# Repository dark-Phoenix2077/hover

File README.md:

# Hover
A fully custom mini racing/stunt drone with ML-assisted balancing, automatic stunts, and some level of autonomous operation without costly cameras or GPS.

## Why I built this

I wanted a challenge that forced me to learn PCB design and embedded firmware from 
scratch, but also let me apply the area I already know well - machine learning. Designing
a drone from a blank schematic, writing every driver by hand, and then training a custom 
tiny ML model felt like the right way to do all of that at once. My goal was simply to push my first ever hardware project as far as I could, not to have a completely polished project.

## What the project is

Hover is a tiny brushed micro quadcopter built entirely from custom hardware and
firmware. There is no off-the-shelf flight controller, no commercial RC receiver, and no
pre-written driver code. Everything was written/designed from scratch by me.

The system has two PCBs:

Flight Controller (FC): A 4-layer X-shaped PCB with a motor in each corner. It runs an
STM32F103C8T6 at 72MHz, an ICM-42688-P IMU over SPI, a BK2423 2.4GHz RF transceiver, 
and four brushed motor drive circuits.

Remote Control (RC): A 2-layer PCB inside a 3D-printed enclosure. It uses
the same STM32F103C8T6 and BK2423 RF ICs. It has two analog joysticks (ADC + DMA) for
throttle, yaw, pitch, and roll, and eight buttons which are used for arming, auto take-off, auto land,
return-to-home, a 360-degree flip trigger (one of my goals for this was to have some kind of smart one-button trick, and for this goal I settled on the 360 flip), and three spares for future use.

apart from that, this repository also includes:

ML Pipeline: A training and conversion pipeline for an onboard stabilisation model.
Training data will be collected from real flight telemetry once the hardware is
bought. The model will be converted to TFLite and dropped directly into the
FC firmware, which already has the inference code in place and waiting.

CAD: Both the drone body and RC enclosure were designed in Onshape. The drone frame
is a minimal 2-shell design with motor mounts, battery tray, and canopy, with both shells 
sandwiching the PCB in the middle. The RC enclosure uses the same 2-shell design with joystick 
cutouts, button extenders, and a battery bay below the PCB.

Firmware: Firmware created for both the FC and RC in STM32 CubeMX and CubeIDE, all firmware should work but is untested as I do not have the hardware right now. additionally, the ML inference file is writtenbut will not work until I create the .tflite model file.

BOM: A BOM generated from kicad for the FC & the RC and also other parts (excluding 3D printed parts and assorted screws). I will likely be purchasing all of these myself, and this is not completely final.

## Build Photos:

# Bill of Materials
FC

* Note that MPU-6050 is significantly cheaper locally, and that is why I chose to use it despite cheaper alternatives

| Reference | Component | Qty | Package | LCSC | Price/Unit |
|---|---|---|---|---|---|
| U2 | STM32F103C8T6 | 1 | LQFP-48 | https://www.lcsc.com/product-detail/C8734.html | $1.65 |
| U3 | MPU-6050 | 1 | QFN-24 | https://www.lcsc.com/product-detail/C24112.html | $6.88 |
| U4 | BK2423 | 1 | QFN-20 | https://www.lcsc.com/search?q=BK2423 | ~$0.80 |
| U1 | AMS1117-3.3 | 1 | SOT-223 | https://www.lcsc.com/product-detail/C347222.html | ~$0.10 |
| Y1, Y2 | 16MHz Crystal | 2 | SMD 3225-4Pin | https://www.lcsc.com/product-detail/C13738.html | $0.30 |
| Q1–Q4 | SI2300 MOSFET | 4 | SOT-23 | https://www.lcsc.com/product-detail/C6285728.html | $0.01 |
| D1–D4 | 1N4148 Flyback Diode | 4 | SOD-323 | https://www.lcsc.com/product-detail/C2972761.html | $0.006 |
| J1 | Battery Connector (1S) | 1 | JST-PH 2pin | https://www.lcsc.com/product-detail/C295747.html | ~$0.08 |
| J2–J5 | Motor Connector | 4 | JST-PH 2pin | https://www.lcsc.com/product-detail/C295747.html | ~$0.08 |
| J6 | SWD Header | 1 | 2.54mm 1×4 | https://www.lcsc.com/product-detail/C124375.html | ~$0.05 |
| J7 | Charge Port | 1 | Barrel Jack SMD | www.lcsc.com/product-detail/C16214.html | ~$0.20 |
| SW1 | Slide Switch | 1 | SMD SPDT | https://www.lcsc.com/product-detail/C431541.html | ~$0.12 |
| TP1–TP5 | Test Point 1.5mm | 5 | Pad D1.5mm | https://www.lcsc.com/search?q=testpoint+1.5mm | ~$0.02 |
| C1, C3, C19, C21 | 10µF Cap | 4 | 0805 | https://www.lcsc.com/search?q=0805+capacitor | ~$0.002 |
| C2, C4–C10, C14–C18, C20, C24 | 100nF Cap | 15 | 0402 | https://www.lcsc.com/search?q=0402+capacitor | ~$0.002 |
| C11 | 1µF Cap | 1 | 0402 | https://www.lcsc.com/search?q=0402+capacitor | ~$0.002 |
| C12, C13, C22, C23 | 22pF Cap | 4 | 0402 | https://www.lcsc.com/search?q=0402+capacitor | ~$0.002 |
| R1, R6, R8, R10, R12 | 10kΩ Resistor | 5 | 0402 | https://www.lcsc.com/search?q=0402+resistor | ~$0.002 |
| R2, R3 | 4.7kΩ Resistor | 2 | 0402 | https://www.lcsc.com/search?q=0402+resistor | ~$0.002 |
| R4 | 22kΩ Resistor | 1 | 0402 | https://www.lcsc.com/search?q=0402+resistor | ~$0.002 |
| R5, R7, R9, R11 | 100Ω Resistor | 4 | 0402 | https://www.lcsc.com/search?q=0402+resistor | ~$0.002 |

RC

| Reference | Component | Qty | Package | LCSC | Price/Unit |
|---|---|---|---|---|---|
| U4 | STM32F103C8T6 | 1 | LQFP-48 | https://www.lcsc.com/product-detail/C8734.html | $1.65 |
| U5 | BK2423 | 1 | QFN-20 | https://www.lcsc.com/search?q=BK2423 | ~$0.80 |
| U1 | AMS1117-3.3 | 1 | SOT-223 | https://www.lcsc.com/product-detail/C347222.html | ~$0.10 |
| Y2, Y3 | 16MHz Crystal | 2 | SMD 3225-4Pin | https://www.lcsc.com/product-detail/C13738.html | $0.30 |
| BZ1 | Buzzer | 1 | 12×9.5mm THT | — | — |
| D1 | LED Indicator | 1 | THT D1.8mm | — | — |
| J1 | Battery Connector (1S) | 1 | JST-PH 2pin | https://www.lcsc.com/product-detail/C295747.html | ~$0.08 |
| J2, J3 | Joystick Connector | 2 | 2.54mm 1×5 | — | — |
| J7 | SWD Header | 1 | 2.54mm 1×4 | https://www.lcsc.com/product-detail/C124375.html | ~$0.05 |
| J8 | Charge Port | 1 | Barrel Jack THT | https://www.lcsc.com/product-detail/C16214.html | ~$0.20 |
| SW1–SW8 | Push Button | 8 | THT 6mm | — | — |
| SW9 | Slide Switch | 1 | SMD SPDT | https://www.lcsc.com/product-detail/C431541.html | ~$0.12 |
| TP1 | Test Point 1.5mm (ANT) | 1 | Pad D1.5mm | https://www.lcsc.com/search?q=testpoint+1.5mm | ~$0.02 |
| C1, C3, C23, C31 | 10µF Cap | 4 | 0805 | https://www.lcsc.com/search?q=0805+capacitor | ~$0.002 |
| C2, C4, C14–C19, C24, C25, C28–C30 | 100nF Cap | 13 | 0402 | https://www.lcsc.com/search?q=0402+capacitor | ~$0.002 |
| C20 | 1µF Cap | 1 | 0402 | https://www.lcsc.com/search?q=0402+capacitor | ~$0.002 |
| C21, C22, C26, C27 | 22pF Cap | 4 | 0402 | https://www.lcsc.com/search?q=0402+capacitor | ~$0.002 |
| R1–R3 | 10kΩ Resistor | 3 | 0402 | https://www.lcsc.com/search?q=0402+resistor | ~$0.002 |
| R4 | 22kΩ Resistor | 1 | 0402 | https://www.lcsc.com/search?q=0402+resistor | ~$0.002 |
| R5, R6 | 100Ω Resistor | 2 | 0402 | https://www.lcsc.com/search?q=0402+resistor | ~$0.002 |

Other

* This list covers physical assembly components not part of either PCB
* It is not completely final - I made this off the top of my head, there are probably other components I forgot to identify
* It does not include miscellaneous screws or 3D printed parts

| Component | Qty | Notes | Price (est.) |
|---|---|---|---|
| Brushed coreless DC motors (8020) | 4 | 8×20mm form factor, 1S compatible | ~$2.00 each |
| 55mm micro quad propellers (CW) | 4 | Match motor shaft diameter | ~$0.50 each |
| 55mm micro quad propellers (CCW) | 4 | Match motor shaft diameter | ~$0.50 each |
| 1S LiPo battery — 150mAh (drone) | 1 | Fits battery tray in drone frame | ~$4.00 |
| 1S LiPo battery — 800mAh (RC) | 1 | Fits battery bay in RC enclosure | ~$6.00 |
| 31.25mm wire for 2.4GHz antenna (drone) | 1 | Bare solid-core wire, soldered to ANT test point on FC PCB; length = λ/4 at 2.4GHz | ~$0.10 |
| 31.25mm wire for 2.4GHz antenna (RC) | 1 | Same as above, for RC PCB ANT test point | ~$0.10 |
| Silicone motor wire (26AWG) | ~1m | Connects motors to PCB JST connectors | ~$1.00 |
| 1S LiPo charger (USB) | 1 | Compatible with JST-PH or barrel jack input | ~$5.00 |

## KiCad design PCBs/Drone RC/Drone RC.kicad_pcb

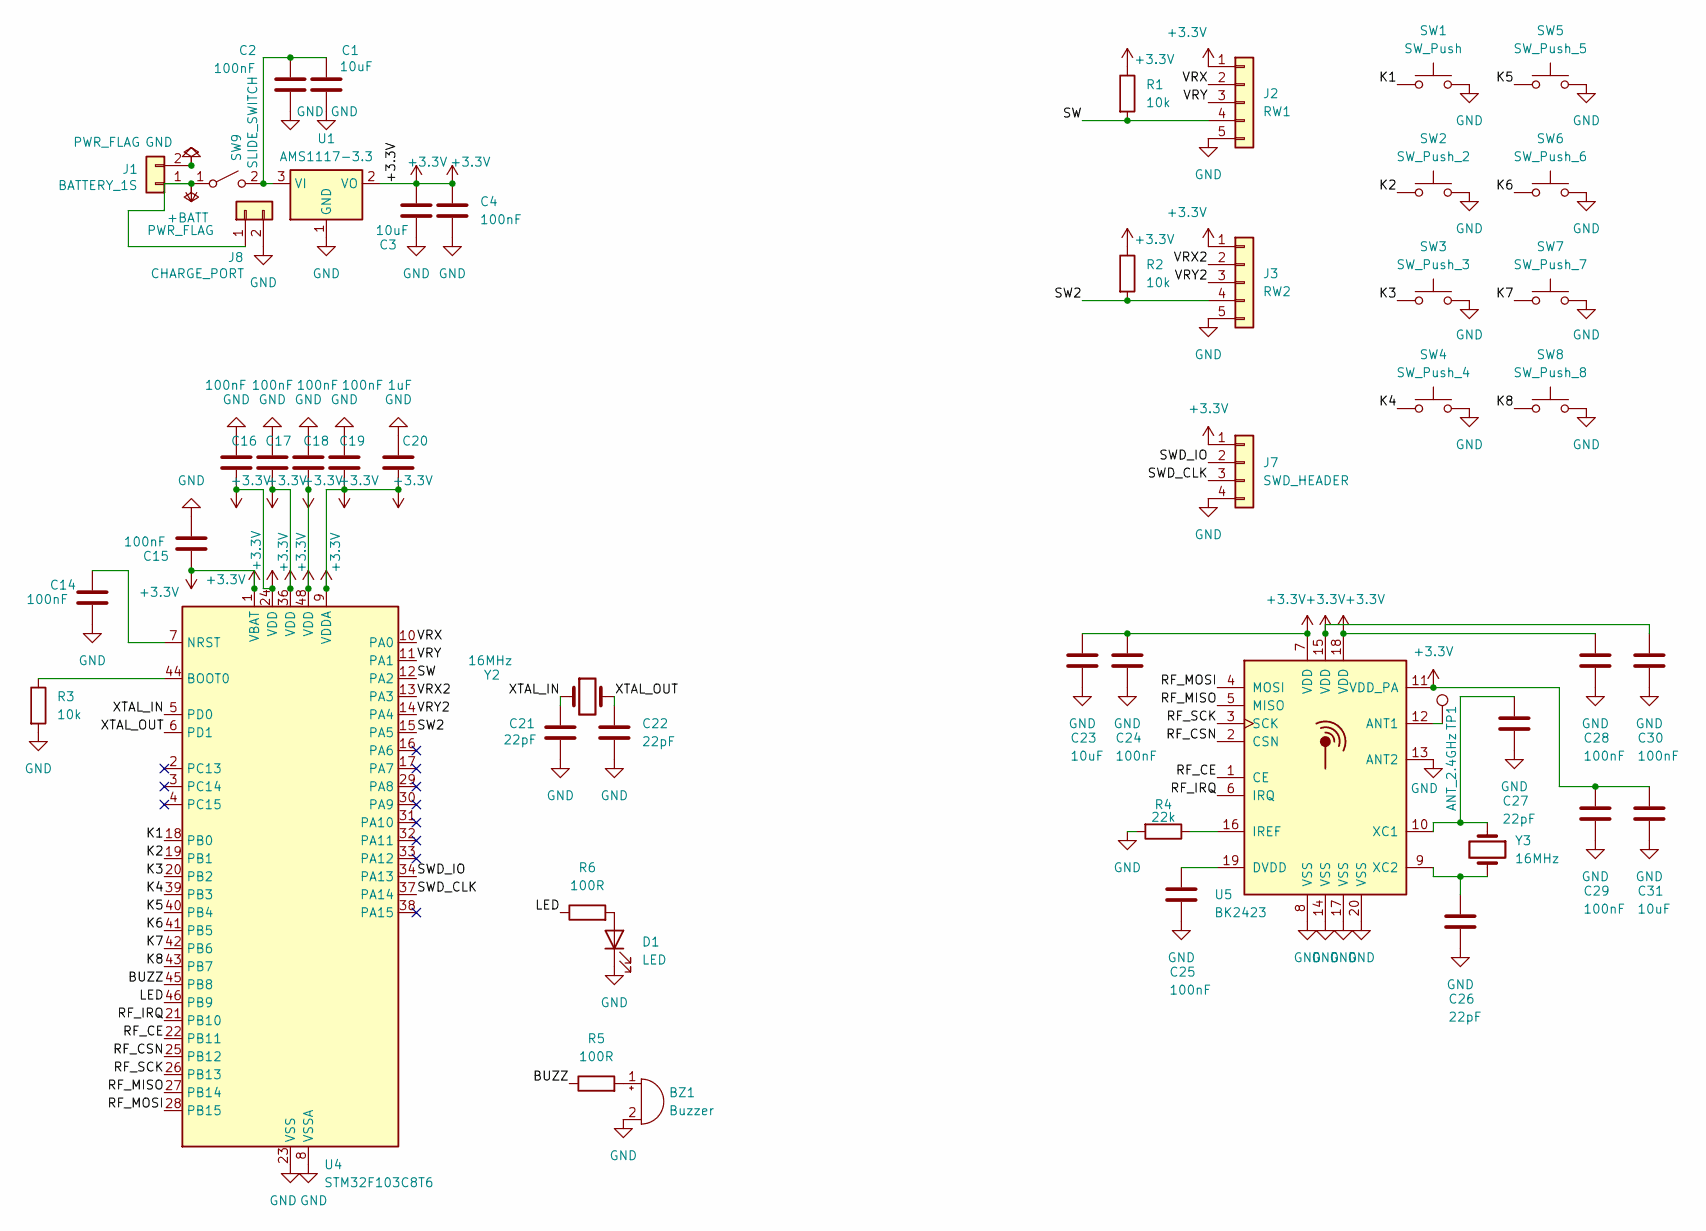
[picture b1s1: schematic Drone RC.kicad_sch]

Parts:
BZ1: Buzzer; Buzzer_12x9.5RM7.6
C1, C3, C23, C31: 10uF; C_0805_2012Metric
C2, C4, C14, C15, C16, C17, C18, C19, C24, C25, C28, C29, C30: 100nF; C_0402_1005Metric
C20: 1uF; C_0402_1005Metric
C21, C22, C26, C27: 22pF; C_0402_1005Metric
D1: LED; LED_D1.8mm_W1.8mm_H2.4mm_Horizontal_O1.27mm_Z1.6mm
J1: BATTERY_1S; JST_PH_B2B-PH-K_1x02_P2.00mm_Vertical
J2: RW1; PinHeader_1x05_P2.54mm_Vertical
J3: RW2; PinHeader_1x05_P2.54mm_Vertical
J7: SWD_HEADER; PinHeader_1x04_P2.54mm_Vertical
J8: CHARGE_PORT; BarrelJack_CUI_PJ-102AH_Horizontal
R1, R2, R3: 10k; R_0402_1005Metric
R4: 22k; R_0402_1005Metric
R5, R6: 100R; R_0402_1005Metric
SW1: SW_Push; SW_PUSH_6mm
SW2: SW_Push_2; SW_PUSH_6mm
SW3: SW_Push_3; SW_PUSH_6mm
SW4: SW_Push_4; SW_PUSH_6mm
SW5: SW_Push_5; SW_PUSH_6mm
SW6: SW_Push_6; SW_PUSH_6mm
SW7: SW_Push_7; SW_PUSH_6mm
SW8: SW_Push_8; SW_PUSH_6mm
SW9: SLIDE_SWITCH; SW_SPDT_CK_JS102011SAQN
TP1: ANT_2.4GHz; TestPoint_Pad_D1.5mm
U1: AMS1117-3.3; SOT-223-3_TabPin2
U4: STM32F103C8T6; LQFP-48_7x7mm_P0.5mm
U5: BK2423; QFN-20-1EP_4x4mm_P0.5mm_EP2.5x2.5mm
Y2, Y3: 16MHz; Crystal_SMD_3225-4Pin_3.2x2.5mm

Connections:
+3.3V: C3.1, C4.1, C15.1, C16.1, C17.1, C18.1, C19.1, C20.1, C23.1, C24.1, C28.1, C29.1, C30.1, C31.1, J2.1, J3.1, J7.1, R1.1, R2.1, U1.2 (VO), U4.1 (VBAT), U4.9 (VDDA), U4.24 (VDD), U4.36 (VDD), U4.48 (VDD), U5.7 (VDD), U5.11 (VDD_PA), U5.15 (VDD), U5.18 (VDD)
+BATT: J1.1, J8.1, SW9.1 (A)
/BUZZ: R5.1, U4.45 (PB8)
/K1: SW1.1, U4.18 (PB0)
/K2: SW2.1, U4.19 (PB1)
/K3: SW3.1, U4.20 (PB2)
/K4: SW4.1, U4.39 (PB3)
/K5: SW5.1, U4.40 (PB4)
/K6: SW6.1, U4.41 (PB5)
/K7: SW7.1, U4.42 (PB6)
/K8: SW8.1, U4.43 (PB7)
/LED: R6.1, U4.46 (PB9)
/RF_CE: U4.22 (PB11), U5.1 (CE)
/RF_CSN: U4.25 (PB12), U5.2 (CSN)
/RF_IRQ: U4.21 (PB10), U5.6 (IRQ)
/RF_MISO: U4.27 (PB14), U5.5 (MISO)
/RF_MOSI: U4.28 (PB15), U5.4 (MOSI)
/RF_SCK: U4.26 (PB13), U5.3 (SCK)
/SW: J2.4, R1.2, U4.12 (PA2)
/SW2: J3.4, R2.2, U4.15 (PA5)
/SWD_CLK: J7.3, U4.37 (PA14)
/SWD_IO: J7.2, U4.34 (PA13)
/VRX: J2.2, U4.10 (PA0)
/VRX2: J3.2, U4.13 (PA3)
/VRY: J2.3, U4.11 (PA1)
/VRY2: J3.3, U4.14 (PA4)
/XTAL_IN: C21.1, U4.5 (PD0), Y2.1
/XTAL_OUT: C22.1, U4.6 (PD1), Y2.2
GND: BZ1.2 (-), C1.2, C2.2, C3.2, C4.2, C14.2, C15.2, C16.2, C17.2, C18.2, C19.2, C20.2, C21.2, C22.2, C23.2, C24.2, C25.2, C26.2, C27.2, C28.2, C29.2, C30.2, C31.2, D1.1 (K), J1.2, J2.5, J3.5, J7.4, J8.2, R3.2, R4.2, SW1.2, SW2.2, SW3.2, SW4.2, SW5.2, SW6.2, SW7.2, SW8.2, U1.1 (GND), U4.8 (VSSA), U4.23 (VSS), U4.35 (VSS), U4.47 (VSS), U5.8 (VSS), U5.13 (ANT2), U5.14 (VSS), U5.17 (VSS), U5.20 (VSS)
unnamed: BZ1.1 (+), R5.2
unnamed: D1.2 (A), R6.2
unnamed: C1.1, C2.1, SW9.2 (B), U1.3 (VI)
unnamed: R3.1, U4.44 (BOOT0)
unnamed: C14.1, U4.7 (NRST)
unnamed: TP1.1 (1_1), U5.12 (ANT1)
unnamed: C25.1, U5.19 (DVDD)
unnamed: R4.1, U5.16 (IREF)
unnamed: C27.1, U5.10 (XC1), Y3.1
unnamed: C26.1, U5.9 (XC2), Y3.2

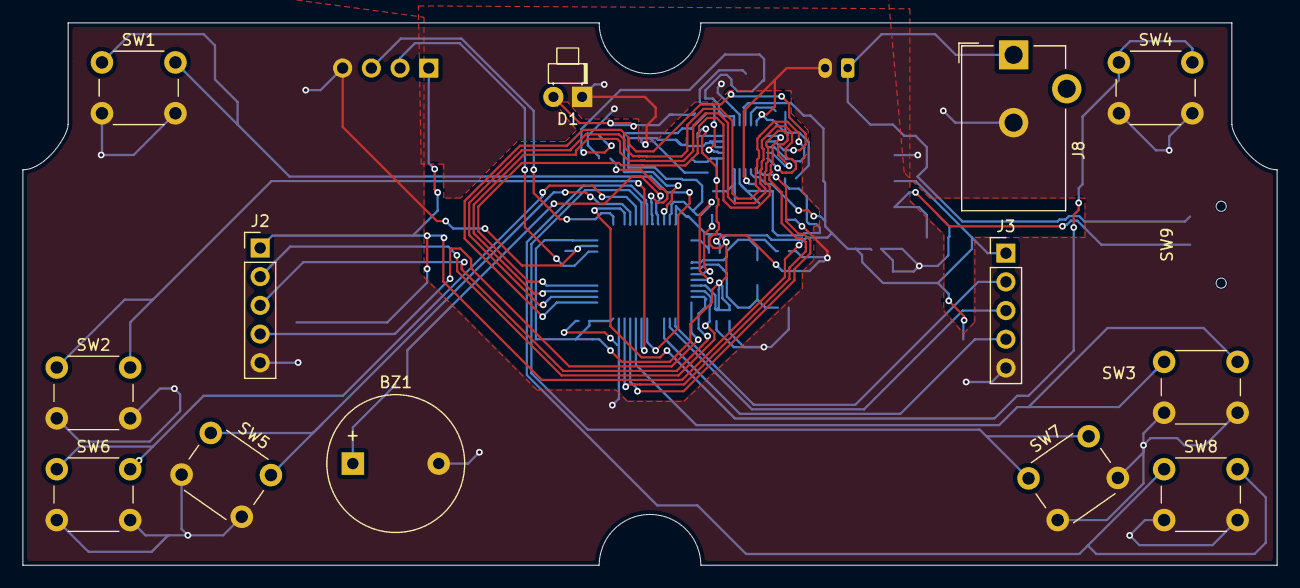
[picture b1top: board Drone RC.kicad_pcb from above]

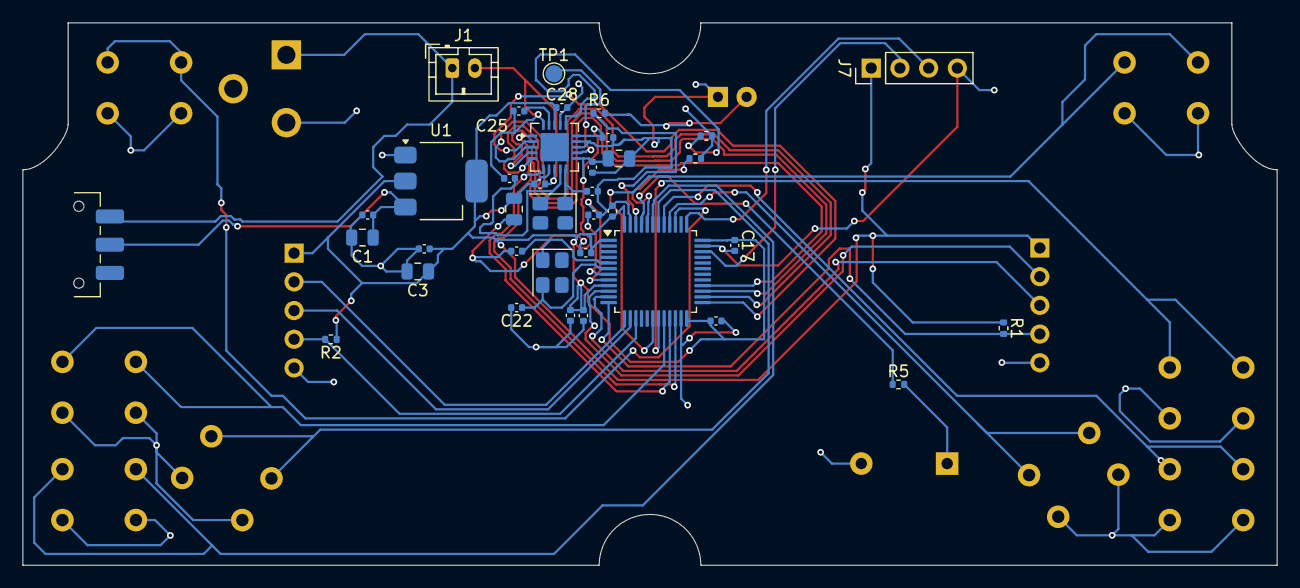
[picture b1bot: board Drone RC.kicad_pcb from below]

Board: 2 copper layers, 111.0 x 48.0 mm, 50 parts (37 on the bottom side), 39 nets.

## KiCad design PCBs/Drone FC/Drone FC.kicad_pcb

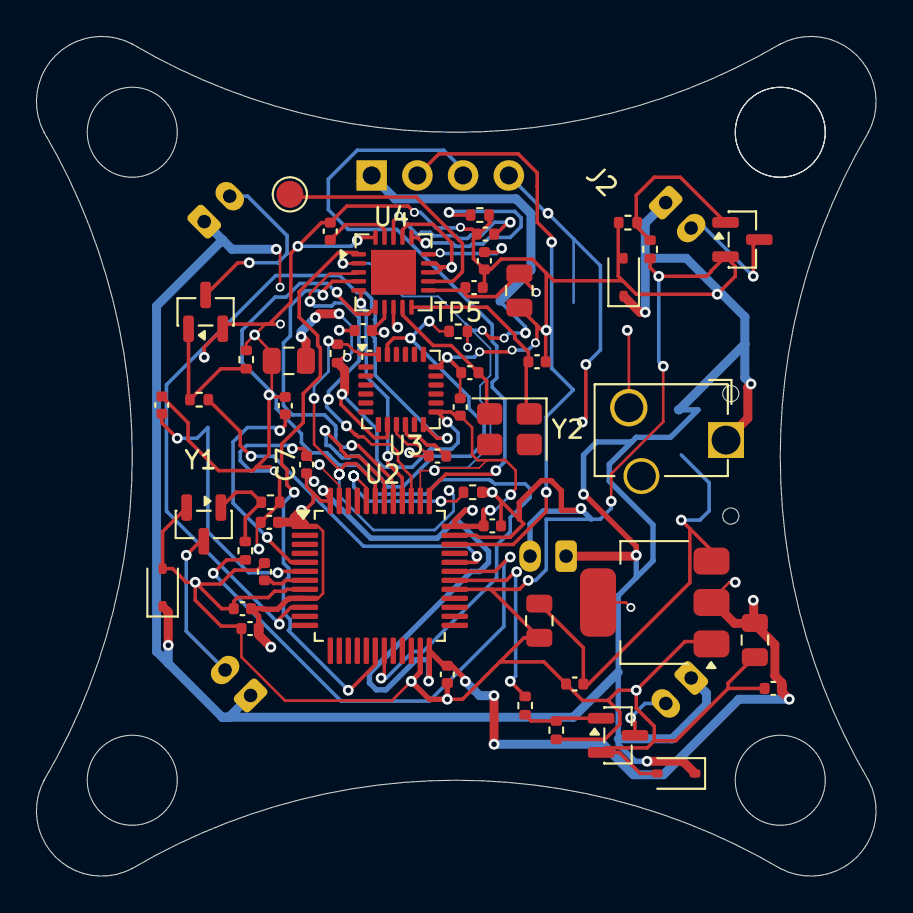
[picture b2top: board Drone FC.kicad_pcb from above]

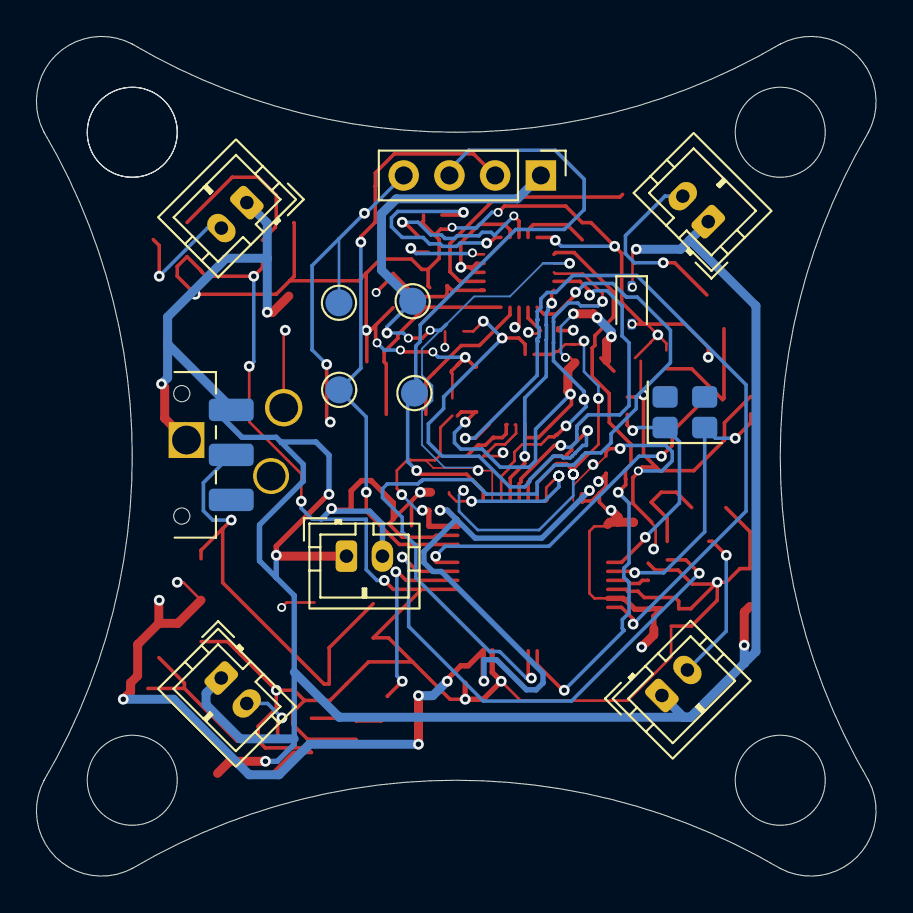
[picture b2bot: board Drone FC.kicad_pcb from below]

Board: 4 copper layers, 46.6 x 46.6 mm, 63 parts (13 on the bottom side), 37 nets.

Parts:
C1, C3, C19, C21: 10uF; C_0805_2012Metric
C2, C4, C5, C6, C7, C8, C9, C10, C14, C15, C16, C17, C18, C20, C24: 100nF; C_0402_1005Metric
C11: 1uF; C_0402_1005Metric
C12, C13, C22, C23: 22pF; C_0402_1005Metric
D1, D2, D3, D4: 1N4148; D_SOD-323
J1: BATTERY_1S; JST_PH_B2B-PH-K_1x02_P2.00mm_Vertical
J2: MOTOR1; JST_PH_B2B-PH-K_1x02_P2.00mm_Vertical
J3: MOTOR2; JST_PH_B2B-PH-K_1x02_P2.00mm_Vertical
J4: MOTOR3; JST_PH_B2B-PH-K_1x02_P2.00mm_Vertical
J5: MOTOR4; JST_PH_B2B-PH-K_1x02_P2.00mm_Vertical
J6: SWD_HEADER; PinHeader_1x04_P2.54mm_Vertical
J7: CHARGE_PORT; DC-011D_SMD_Horizontal
Q1, Q2, Q3, Q4: SI2300; SOT-23
R1, R6, R8, R10, R12: 10k; R_0402_1005Metric
R2, R3: 4.7k; R_0402_1005Metric
R4: 22k; R_0402_1005Metric
R5, R7, R9, R11: 100R; R_0402_1005Metric
SW1: SLIDE_SWITCH; SW_SPDT_CK_JS102011SAQN
TP1: ANT_2.4GHz; TestPoint_Pad_D1.5mm
TP2: D; TestPoint_Pad_D1.5mm
TP3: C; TestPoint_Pad_D1.5mm
TP4: GND; TestPoint_Pad_D1.5mm
TP5: VCC; TestPoint_Pad_D1.5mm
U1: AMS1117-3.3; SOT-223-3_TabPin2
U2: STM32F103C8T6; LQFP-48_7x7mm_P0.5mm
U3: MPU-6050; InvenSense_QFN-24_4x4mm_P0.5mm
U4: BK2423; QFN-20-1EP_4x4mm_P0.5mm_EP2.5x2.5mm
Y1, Y2: 16MHz; Crystal_SMD_3225-4Pin_3.2x2.5mm

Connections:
+3.3V: C16.1, C17.1, C18.1, C20.1, C21.1, R3.1, U1.2 (VO), U4.7 (VDD), U4.11 (VDD_PA), U4.15 (VDD), U4.18 (VDD)
+BATT: D1.1 (K), D2.1 (K), D3.1 (K), D4.1 (K), J1.1, J2.1, J3.1, J4.1, J5.1, J7.1, SW1.1 (A)
/IMU_INT: U2.10 (PA0), U3.12 (INT)
/IMU_SCL: R3.2, U2.42 (PB6), U3.23 (SCL)
/IMU_SDA: R2.2, U2.43 (PB7), U3.24 (SDA)
/MOTOR1_PWM: C1.2, C2.2, C3.2, C4.2, C5.2, C6.2, C7.2, C8.2, C9.2, C10.2, C11.2, C12.2, C13.2, C14.2, C16.2, C17.2, C19.2, C20.2, C21.2, C22.2, C23.2, C24.2, D1.2 (A), D2.2 (A), D3.2 (A), D4.2 (A), J1.2, Q1.2 (S), Q2.2 (S), Q3.2 (S), Q4.2 (S), R1.2, R4.2, R5.2, R6.2, R8.2, R10.2, R12.2, U1.1 (GND), U2.8 (VSSA), U2.23 (VSS), U2.29 (PA8), U2.35 (VSS), U2.47 (VSS), U3.18 (GND), U4.20 (VSS)
/MOTOR2_PWM: R7.2, U2.30 (PA9)
/MOTOR3_PWM: R9.2, U2.31 (PA10)
/MOTOR4_PWM: R11.2, U2.32 (PA11)
/RF_CE: U2.18 (PB0), U4.1 (CE)
/RF_CSN: C3.1, C4.1, C5.1, C6.1, C7.1, C8.1, C10.1, C11.1, C14.1, C19.1, J6.1, R2.1, TP5.1 (1_1), U1.2 (VO), U2.1 (VBAT), U2.9 (VDDA), U2.24 (VDD), U2.36 (VDD), U2.38 (PA15), U2.48 (VDD), U3.8 (VLOGIC), U3.13 (VDD), U4.2 (CSN)
/RF_IRQ: U2.19 (PB1), U4.6 (IRQ)
/RF_MISO: U2.40 (PB4), U4.5 (MISO)
/RF_MOSI: U2.41 (PB5), U4.4 (MOSI)
/RF_SCK: U2.39 (PB3), U4.3 (SCK)
/SWD_CLK: J6.3, TP3.1 (1_1), U2.37 (PA14)
/SWD_IO: J6.2, TP2.1 (1_1), U2.34 (PA13)
/XTAL_IN: C12.1, U2.5 (PD0), Y1.1
/XTAL_OUT: C13.1, U2.6 (PD1), Y1.2
GND: C15.2, C18.2, J6.4, J7.2, TP4.1 (1_1), U3.9 (AD0), U4.8 (VSS), U4.13 (ANT2), U4.14 (VSS), U4.17 (VSS)
unnamed: J2.2, Q1.3 (D)
unnamed: J3.2, Q2.3 (D)
unnamed: J4.2, Q3.3 (D)
unnamed: J5.2, Q4.3 (D)
unnamed: Q1.1 (G), R5.1, R6.1
unnamed: Q2.1 (G), R7.1, R8.1
unnamed: Q3.1 (G), R9.1, R10.1
unnamed: Q4.1 (G), R11.1, R12.1
unnamed: C1.1, C2.1, SW1.2 (B), U1.3 (VI)
unnamed: R1.1, U2.44 (BOOT0)
unnamed: C9.1, U2.7 (NRST)
unnamed: C15.1, U3.10 (REGOUT)
unnamed: TP1.1 (1_1), U4.12 (ANT1)
unnamed: C24.1, U4.19 (DVDD)
unnamed: R4.1, U4.16 (IREF)
unnamed: C22.1, U4.10 (XC1), Y2.1
unnamed: C23.1, U4.9 (XC2), Y2.2

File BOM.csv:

Board,Reference,Component,Qty,Package,LCSC Link,Price/Unit
FC,U2,STM32F103C8T6,1,LQFP-48,https://www.lcsc.com/product-detail/C8734.html,$1.65
FC,U3,MPU-6050,1,QFN-24,https://www.lcsc.com/product-detail/C24112.html,$6.88
FC,U4,BK2423,1,QFN-20,https://www.lcsc.com/search?q=BK2423,~$0.80
FC,U1,AMS1117-3.3,1,SOT-223,https://www.lcsc.com/product-detail/C347222.html,~$0.10
FC,"Y1, Y2",16MHz Crystal,2,SMD 3225-4Pin,https://www.lcsc.com/product-detail/C13738.html,$0.30
FC,Q1–Q4,SI2300 MOSFET,4,SOT-23,https://www.lcsc.com/product-detail/C6285728.html,$0.01
FC,D1–D4,1N4148 Flyback Diode,4,SOD-323,https://www.lcsc.com/product-detail/C2972761.html,$0.006
FC,J1,Battery Connector (1S),1,JST-PH 2pin,https://www.lcsc.com/product-detail/C295747.html,~$0.08
FC,J2–J5,Motor Connector,4,JST-PH 2pin,https://www.lcsc.com/product-detail/C295747.html,~$0.08
FC,J6,SWD Header,1,2.54mm 1×4,https://www.lcsc.com/product-detail/C124375.html,~$0.05
FC,J7,Charge Port,1,Barrel Jack SMD,https://www.lcsc.com/product-detail/C16214.html,~$0.20
FC,SW1,Slide Switch,1,SMD SPDT,https://www.lcsc.com/product-detail/C431541.html,~$0.12
FC,TP1–TP5,Test Point 1.5mm,5,Pad D1.5mm,https://www.lcsc.com/search?q=testpoint+1.5mm,~$0.02
FC,"C1, C3, C19, C21",10µF Cap,4,0805,https://www.lcsc.com/search?q=0805+capacitor,~$0.002
FC,"C2, C4–C10, C14–C18, C20, C24",100nF Cap,15,0402,https://www.lcsc.com/search?q=0402+capacitor,~$0.002
FC,C11,1µF Cap,1,0402,https://www.lcsc.com/search?q=0402+capacitor,~$0.002
FC,"C12, C13, C22, C23",22pF Cap,4,0402,https://www.lcsc.com/search?q=0402+capacitor,~$0.002
FC,"R1, R6, R8, R10, R12",10kΩ Resistor,5,0402,https://www.lcsc.com/search?q=0402+resistor,~$0.002
FC,"R2, R3",4.7kΩ Resistor,2,0402,https://www.lcsc.com/search?q=0402+resistor,~$0.002
FC,R4,22kΩ Resistor,1,0402,https://www.lcsc.com/search?q=0402+resistor,~$0.002
FC,"R5, R7, R9, R11",100Ω Resistor,4,0402,https://www.lcsc.com/search?q=0402+resistor,~$0.002
RC,U4,STM32F103C8T6,1,LQFP-48,https://www.lcsc.com/product-detail/C8734.html,$1.65
RC,U5,BK2423,1,QFN-20,https://www.lcsc.com/search?q=BK2423,~$0.80
RC,U1,AMS1117-3.3,1,SOT-223,https://www.lcsc.com/product-detail/C347222.html,~$0.10
RC,"Y2, Y3",16MHz Crystal,2,SMD 3225-4Pin,https://www.lcsc.com/product-detail/C13738.html,$0.30
RC,BZ1,Buzzer,1,12×9.5mm THT,https://www.lcsc.com/product-detail/C96093.html,~$0.50
RC,D1,LED Indicator,1,THT D1.8mm,https://www.lcsc.com/search?q=LED+1.8mm+THT,~$0.05
RC,J1,Battery Connector (1S),1,JST-PH 2pin,https://www.lcsc.com/product-detail/C295747.html,~$0.08
RC,"J2, J3",Joystick Connector,2,2.54mm 1×5,https://www.lcsc.com/search?q=2.54mm+1x5+header,~$0.05
RC,J7,SWD Header,1,2.54mm 1×4,https://www.lcsc.com/product-detail/C124375.html,~$0.05
RC,J8,Charge Port,1,Barrel Jack THT,https://www.lcsc.com/product-detail/C16214.html,~$0.20
RC,SW1–SW8,Push Button,8,THT 6mm,https://www.lcsc.com/product-detail/C285474.html,~$0.10
RC,SW9,Slide Switch,1,SMD SPDT,https://www.lcsc.com/product-detail/C431541.html,~$0.12
RC,TP1,Test Point 1.5mm (ANT),1,Pad D1.5mm,https://www.lcsc.com/search?q=testpoint+1.5mm,~$0.02
RC,"C1, C3, C23, C31",10µF Cap,4,0805,https://www.lcsc.com/search?q=0805+capacitor,~$0.002
RC,"C2, C4, C14–C19, C24, C25, C28–C30",100nF Cap,13,0402,https://www.lcsc.com/search?q=0402+capacitor,~$0.002
RC,C20,1µF Cap,1,0402,https://www.lcsc.com/search?q=0402+capacitor,~$0.002
RC,"C21, C22, C26, C27",22pF Cap,4,0402,https://www.lcsc.com/search?q=0402+capacitor,~$0.002
RC,R1–R3,10kΩ Resistor,3,0402,https://www.lcsc.com/search?q=0402+resistor,~$0.002
RC,R4,22kΩ Resistor,1,0402,https://www.lcsc.com/search?q=0402+resistor,~$0.002
RC,"R5, R6",100Ω Resistor,2,0402,https://www.lcsc.com/search?q=0402+resistor,~$0.002
Other,—,Brushed coreless DC motors (8020),4,8×20mm,https://www.lcsc.com/search?q=8020+coreless+motor,~$2.00
Other,—,55mm micro quad propellers (CW),4,55mm,https://www.lcsc.com/search?q=55mm+propeller+CW,~$0.50
Other,—,55mm micro quad propellers (CCW),4,55mm,https://www.lcsc.com/search?q=55mm+propeller+CCW,~$0.50
Other,—,1S LiPo battery — 150mAh (drone),1,—,https://www.lcsc.com/search?q=1S+150mAh+lipo,~$4.00
Other,—,1S LiPo battery — 800mAh (RC),1,—,https://www.lcsc.com/search?q=1S+800mAh+lipo,~$6.00
Other,—,31.25mm wire for 2.4GHz antenna (drone),1,—,https://www.lcsc.com/search?q=solid+core+wire,~$0.10
Other,—,31.25mm wire for 2.4GHz antenna (RC),1,—,https://www.lcsc.com/search?q=solid+core+wire,~$0.10
Other,—,Silicone motor wire (26AWG),1,~1m,https://www.lcsc.com/search?q=26AWG+silicone+wire,~$1.00
Other,—,1S LiPo charger (USB),1,—,https://www.lcsc.com/search?q=1S+lipo+USB+charger,~$5.00

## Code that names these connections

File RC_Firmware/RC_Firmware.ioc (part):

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Mcu.Name=STM32F103C(8-B)Tx
Mcu.Package=LQFP48
Mcu.UserName=STM32F103C8Tx
PA0-WKUP.Signal=ADCx_IN0
PA1.Signal=ADCx_IN1
PA10.Mode=Asynchronous
PA10.Signal=USART1_RX
PA11.GPIOParameters=GPIO_Label
PA11.GPIO_Label=BTN_ARM
PA11.Signal=GPIO_Input
PA12.GPIOParameters=GPIO_Label
PA12.GPIO_Label=BTN_FLIP
PA12.Signal=GPIO_Input
PA13.Mode=Serial_Wire
PA13.Signal=SYS_JTMS-SWDIO
PA14.Mode=Serial_Wire
PA14.Signal=SYS_JTCK-SWCLK
PA2.Signal=ADCx_IN2
PA3.Signal=ADCx_IN3
PA4.Signal=ADCx_IN4
PA5.Mode=Full_Duplex_Master
PA5.Signal=SPI1_SCK
PA6.Mode=Full_Duplex_Master
PA6.Signal=SPI1_MISO
PA7.Mode=Full_Duplex_Master
PA7.Signal=SPI1_MOSI
PA8.GPIOParameters=GPIO_Label
PA8.GPIO_Label=RF_CE
PA8.Signal=GPIO_Output
PA9.Mode=Asynchronous
PA9.Signal=USART1_TX
PB0.GPIOParameters=GPIO_Label
PB0.GPIO_Label=RF_CSN
PB0.Signal=GPIO_Output
PB1.GPIOParameters=GPIO_Label
PB1.GPIO_Label=RF_IRQ
PB1.Signal=GPIO_Input
PB3.GPIOParameters=GPIO_Label
PB3.GPIO_Label=BTN_SP1
PB3.Signal=GPIO_Input
PB4.GPIOParameters=GPIO_Label
PB4.GPIO_Label=BTN_SP2
PB4.Signal=GPIO_Input
PB5.GPIOParameters=GPIO_Label
PB5.GPIO_Label=BTN_SP3
PB5.Signal=GPIO_Input
PB6.GPIOParameters=GPIO_Label
PB6.GPIO_Label=BTN_LAND
PB6.Signal=GPIO_Input
PB7.GPIOParameters=GPIO_Label
PB7.GPIO_Label=BTN_TKOFF
PB7.Signal=GPIO_Input
PB8.GPIOParameters=GPIO_Label
PB8.GPIO_Label=BTN_RTH
PB8.Signal=GPIO_Input
PB9.GPIOParameters=GPIO_Label
PB9.GPIO_Label=BUZZ
PB9.Signal=GPIO_Output
PD0-OSC_IN.Mode=HSE-External-Oscillator
PD0-OSC_IN.Signal=RCC_OSC_IN
PD1-OSC_OUT.Mode=HSE-External-Oscillator
PD1-OSC_OUT.Signal=RCC_OSC_OUT
RCC.SYSCLKFreq_VALUE=72000000
RCC.SYSCLKSource=RCC_SYSCLKSOURCE_PLLCLK
board=custom

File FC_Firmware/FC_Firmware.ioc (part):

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Mcu.Name=STM32F103C(8-B)Tx
Mcu.Package=LQFP48
Mcu.UserName=STM32F103C8Tx
PA0-WKUP.GPIOParameters=GPIO_Label
PA0-WKUP.GPIO_Label=IMU_INT
PA0-WKUP.Signal=GPIO_Input
PA10.Signal=S_TIM1_CH3
PA11.Signal=S_TIM1_CH4
PA13.Mode=Serial_Wire
PA13.Signal=SYS_JTMS-SWDIO
PA14.Mode=Serial_Wire
PA14.Signal=SYS_JTCK-SWCLK
PA2.Mode=Asynchronous
PA2.Signal=USART2_TX
PA3.Mode=Asynchronous
PA3.Signal=USART2_RX
PA4.GPIOParameters=GPIO_Speed,PinState,GPIO_Label
PA4.GPIO_Label=RF_CSN
PA4.GPIO_Speed=GPIO_SPEED_FREQ_HIGH
PA4.PinState=GPIO_PIN_SET
PA4.Signal=GPIO_Output
PA5.Mode=Full_Duplex_Master
PA5.Signal=SPI1_SCK
PA6.Mode=Full_Duplex_Master
PA6.Signal=SPI1_MISO
PA7.Mode=Full_Duplex_Master
PA7.Signal=SPI1_MOSI
PA8.Signal=S_TIM1_CH1
PA9.Signal=S_TIM1_CH2
PB0.GPIOParameters=GPIO_Speed,PinState,GPIO_Label
PB0.GPIO_Label=RF_CE
PB0.GPIO_Speed=GPIO_SPEED_FREQ_HIGH
PB0.PinState=GPIO_PIN_SET
PB0.Signal=GPIO_Output
PB1.GPIOParameters=GPIO_Label
PB1.GPIO_Label=RF_IRQ
PB1.Signal=GPIO_Input
PB12.GPIOParameters=GPIO_Speed,PinState,GPIO_Label
PB12.GPIO_Label=IMU_CS
PB12.GPIO_Speed=GPIO_SPEED_FREQ_HIGH
PB12.PinState=GPIO_PIN_SET
PB12.Signal=GPIO_Output
PB13.Mode=Full_Duplex_Master
PB13.Signal=SPI2_SCK
PB14.Mode=Full_Duplex_Master
PB14.Signal=SPI2_MISO
PB15.Mode=Full_Duplex_Master
PB15.Signal=SPI2_MOSI
PD0-OSC_IN.Mode=HSE-External-Oscillator
PD0-OSC_IN.Signal=RCC_OSC_IN
PD1-OSC_OUT.Mode=HSE-External-Oscillator
PD1-OSC_OUT.Signal=RCC_OSC_OUT
RCC.HSEDivPLL=RCC_HSE_PREDIV_DIV2
RCC.HSE_VALUE=16000000
RCC.SYSCLKFreq_VALUE=72000000
RCC.SYSCLKSource=RCC_SYSCLKSOURCE_PLLCLK
board=custom

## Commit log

2026-04-16 Initial commit
    PCBs, STEP files, Firmware and ML Pipeline files added
2026-04-16 Enhanced README
    Added a more detailed readme.
2026-04-16 added BOM
2026-04-16 updated BOM
2026-04-16 cleaned up drone FC PCB
2026-04-16 cleaned up drone RC PCB
2026-04-16 added readme images
2026-04-18 added BOM to readme (as requested in the docs)
2026-04-18 Turned BOM into CSV (as requested in docs)
2026-04-21 Update README with PCB update note
    Updated README to reflect recent changes to PCBs after fixing KiCad issues.
2026-04-21 added fixed PCBs
2026-06-28 Fixed README
2026-06-28 Added mp4 video showcasing drone capabilities (test.mp4)
2026-06-30 Added build photos
2026-06-30 Fixed problem with images not showing
